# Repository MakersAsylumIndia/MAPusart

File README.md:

MAPusart
========

USB to UART converter board using CP2102. Micro USB input and 6 pin header output.

License
-------
[CERN Open Hardware Licence v1.2 ]

[CERN Open Hardware Licence v1.2 ]:http://www.ohwr.org/attachments/2388/cern_ohl_v_1_2.txt

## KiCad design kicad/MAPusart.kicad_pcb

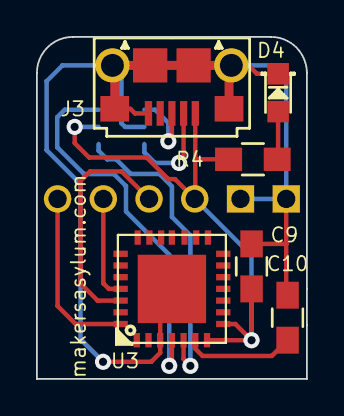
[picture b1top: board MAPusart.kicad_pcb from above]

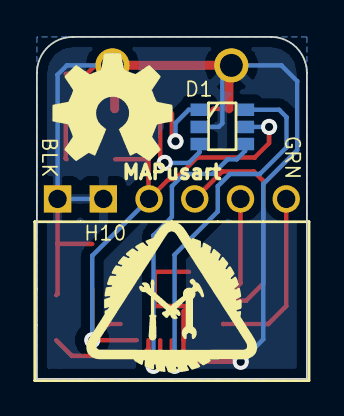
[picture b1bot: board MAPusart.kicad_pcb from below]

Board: 2 copper layers, 15.0 x 19.0 mm, 10 parts (4 on the bottom side), 11 nets.

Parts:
C9, C10: 100n; C_0805_HandSoldering
D1: USBLC6-2; SOT-23-6
D4: LED_USB; LED-0805
H10: FTDI; Socket_Strip_Angled_1x06
J3: USB-Micro; USB_B_Micro
R4: 300E; R_0805_HandSoldering
U3: CP210X; qfn-28
Z3: SCREW; MA_Logo2
Z5: SCREW; OSHW_6mm

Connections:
/3V3: C10.1, U3.6
/5V: C9.1, D1.5, H10.3, J3.1, R4.1, U3.7, U3.8
/D+: D1.6, U3.4
/D+IN: D1.1, J3.3
/D-: D1.4, U3.5
/D-IN: D1.3, J3.2
/GND_U: C9.2, C10.2, D1.2, D4.2, H10.1, H10.2, J3.5, J3.T1, J3.T2, J3.T3, J3.T4, J3.T5, J3.T6, U3.3, U3.29
/RST: H10.6, U3.28
/RXD: H10.5, U3.25
/TXD: H10.4, U3.26
unnamed: D4.1, R4.2

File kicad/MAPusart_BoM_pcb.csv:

"Id";"Designator";"Package";"Quantity";"Designation";"Supplier and ref";
1;"C9,C10";"C_0805_HandSoldering";2;"100n";;;
2;"J3";"USB_B_Micro";1;"USB-Micro";;;
3;"R4";"R_0805_HandSoldering";1;"300E";;;
4;"U3";"qfn-28";1;"CP210X";;;
5;"D4";"LED-0805";1;"LED_USB";;;
6;"H10";"Socket_Strip_Angled_1x06";1;"FTDI";;;
7;"Z3";"MA_Logo2";1;"SCREW";;;
8;"Z5";"OSHW_6mm";1;"SCREW";;;
9;"D1";"SOT-23-6";1;"USBLC6-2";;;

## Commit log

2014-12-02 MAPusart USB <> USART
2014-12-02 MAPusart schematic, PCB complete. Bom pending
2014-12-03 MAPusart complete and ready for prototyping
2014-12-09 MAPusart updated BoM for visha
